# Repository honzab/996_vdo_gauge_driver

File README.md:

# Building an oil temperature gauge for Porsche 996

## Introduction

This project is about building an oil temperature gauge for a Porsche 911/996.

The car does not have a temperature gauge from the factory and neither does it expose the information on 
the CAN bus so that it can be read by an OBD-II reader.

People have developed different kind of solutions for this problem, but there was one that especially
caught my eye, both because of the design but also reversibility and accuracy of the solution.

## tl;dr
There's been some hiccups on the way, but I have succeeded in building a prototype that can display temperature 
values of my choosing. I have a code snippet that runs from 50ºC to 150ºC with a couple of seconds delay 
between each value. The gauge shows the values.

**I have NOT connected anything to the car yet!**

* [Schematics](vdo_gauge_driver_schematics/vdo_gauge_driver_rev0.2.pdf)
* [Code for ATTiny85](vdo_gauge_driver_software/vdo_gauge_driver_software.ino)

## Ahsai's design from 2014

Back in 2014, [Ahsai](https://rennlist.com/forums/members/32590-ahsai.html)
[published a design for a temperature gauge that uses the factory oil level/temperature sensor](https://rennlist.com/forums/996-forum/827720-oil-temp-gauge-using-the-built-in-oil-temp-sensor.html) by
tapping the sensor wire directy on its way to the ECU. This way, the factory ECU is still able to read the oil pressure,
but we can through the tap see it as well.

When you have access to the voltage from the sensor, you can choose to display it in any way you'd like. Back then
Ahsai chose to use the VDO gauge, which fits the design of the interior pretty well.

## Trying to build it in 2025

In April 2025 I decided to try to build it as well.

### Introduction

I looked at the original schematics, but some of the components have already been replaced by newer ones. This meant 
that I would need to redo the schematics, look at all the datasheets and find replacement components.

[Ahsai's Original Schematics](images/ExpressSCH-page-0.jpg)

The circuit itself is fairly simple and smart. It uses an ATTiny85 to convert the voltage from the sensor to a voltage
that drives the VDO gauge.

What we can use from the original design is the values for the sensor signal, or at least the polynomial that 
was used to approximate the conversion values.

### Problem #1, obsolete components

The components in the original design are not available anymore, so we need to find replacements.

For the voltage regulators, that's kind of easy. We can use

* [L7805](datasheets/L78.pdf) for 5V
* ~~[L7812](datasheets/L78.pdf) for 12V (turns out I don't need this one in the end)~~

For the op-amp, the L727M is not available anymore. Moreover it is not rail-to-rail, which means that if the
input drops all the way to 0V, the output will not be able to reach 0V. This is a problem since we need it to
be quite exact.

I set off to find a replacement and found a rail-to-rail op-amp which is easily available.

* [MCP6002](datasheets/mcp6002.pdf)

The microprocessor is still available without problems.

* [ATTiny85](datasheets/attiny85-20pu.pdf)

### Problem #2, the gauge is resistive-type

The original design suggests that you can drive the gauge with voltage. This does not work in reality. The sensor
paired with the gauge seems to be a [NTC thermistor](https://en.wikipedia.org/wiki/Thermistor#NTC_(negative_temperature_coefficient)).

This means that we cannot feed the gauge with the (amplified and converted) voltage from the Porsche sensor.

I am hoping that I can use an N-channel MOSFET to simulate the resistance. This should be drivable by 0-2.5V from the ATTiny85.
Calibration will be needed to get the right display readings.

Right now, I am not really sure how it could ever have worked for Ahsai.

**Solution**: Use a MOSFET to simulate the resistance. I've picked the [2N7000](datasheets/2N7000.pdf) for this.

### Problem 3, the MOSFET is not linear and precise enough

With only the transistor simulating the resistance, I am getting fairly unprecise readings. This is not very good, because
in the beginning of the temperature scale is where I need the most precision, since the oil temperature will likely be
between 50-100°C most of the time.

By making the ATTiny85 output a consistent voltage changes, I could observe the gauge displaying different values depending
on where the needle was moving from.

**Solution**: After a bit of research, it turns out that I could use a current sink with the one op-amp that I have left from the MCP6002.
It was a bit tricky to figure out what the resistor value should be between the source and ground.

#### Problem 3.1, the gauge's internal resistance

Most likely the gauge has some internal resistance and is applying certain voltage on the sensor wire, measuring the voltage drop.

The voltage between the signal pin and ground seems to be 7.5V.

Measuring current using some different resistor values, I got to the following

| R (Ω) | I (mA) | R_int (Ω) |
|-------|--------|-----------|
| 47    | 50     | 103,00    |
| 0     | 59     | 127,12    |

This means, I think, that the internal resistance is likely 100Ω. My cheap multimeter is not very precise, so I am not exactly
sure, but it's at least some ballpark number.

#### Problem 3.2, the current sink values

If we take the above, then we can calculate the currents we want to have through the sensor wire.

* Maximum resistance: 130Ω
* Minimum resistance: 20Ω

Then the currents are:

* Maximum resistance current then: R = 7.5V / 130Ω = 57.69mA
* Minimum resistance current then: R = 7.5V / 20Ω = 375mA

Knowing that we will be driving the MOSFET with a voltage between 0-5V from the ATTiny85, we can calculate
the resistance needed to achieve the above currents, again at least ballpark values.

With R of 22Ω we get these with the different voltages:

| V   | mA          |
|-----|-------------|
| 0,1 | 4,545454545 |
| 1   | 45,45454545 |
| 2   | 90,90909091 |
| 3   | 136,3636364 |
| 4   | 181,8181818 |
| 5   | 227,2727273 |

This is not really exactly what we need, but it is good enough for now. The 5V input would be anyways going over what
the MOSFET can do.

#### Problem 3.3, the op-amp used cannot drive so much current

The MCP6002 op-amp cannot drive as much current as we need. Luckily though, it seems to be able to run the gauge's
pointer all the way to 140ºC, which is good enough for me (for now at least).

### Getting to what value is what

In the original design, Ahsai used Durametric software to get the temperature values (in F) and mapped them to the
voltage observed on the sensor wire.

> [!NOTE]
> I would like to maybe borrow someone's Durametric and check myself. But as of now (May 2025), I trust this data.

[Ahsai's original values](images/Drawing1.jpg), with the polynomial approximated (in F):

```
y = 8.5645 * x^4 - 59.284 * x^3 + 160.76 * x^2 - 245.49x + 299.24
R^2 = 0.9997
```

We can then use this information to build the table of values in Celsius, using a simple [python script](engine_sensor_voltage_temperature.py).
(run `brew install gnuplot` (MacOS) if you don't have it already).

| voltage   | °C       | F       |
|-----------|----------|---------|
| 2.90V     | 37.32°C  | 99.18F  |
| 2.80V     | 36.25°C  | 97.25F  |
| 2.70V     | 35.90°C  | 96.62F  |
| 2.60V     | 36.17°C  | 97.11F  |
| 2.50V     | 36.95°C  | 98.50F  |
| ...        | ...      | ...     |
| 0.40V     | 106.22°C | 223.19F |
| 0.30V     | 114.74°C | 238.53F |
| 0.20V     | 124.51°C | 256.11F |
| 0.10V     | 135.69°C | 276.24F |
| 0.00V     | 148.47°C | 299.24F |

_(I've shortened the table, all the values can be obtained by running the script.)_

### What's needed

TODO: add list of components

#### Mounting

TODO: Could [this be something](https://www.amazon.com/dp/B0018ALWOE/ref=sspa_dk_detail_1?psc=1&pd_rd_i=B0018ALWOE&pd_rd_w=7b38W&content-id=amzn1.sym.7446a9d1-25fe-4460-b135-a60336bad2c9&pf_rd_p=7446a9d1-25fe-4460-b135-a60336bad2c9&pf_rd_r=N8RSV7SSJCJFGKZRW0Q5&pd_rd_wg=nYLRA&pd_rd_r=9f5e788e-8383-43bf-b18c-378f6cef02c4&s=electronics&sp_csd=d2lkZ2V0TmFtZT1zcF9kZXRhaWw)?

#### The DME connectors research

The original Ahsai's links to the connectors point to Mouser, but they are not available anymore.

I think that these should do it, but the only way to know is to order some and try them out.

| type   | old part number | width           | style              | new part number | copied description                                        |
|--------|-----------------|-----------------|--------------------|-----------------|-----------------------------------------------------------|
| male   | 963730-1        | pin 0.63x0.63mm | Micro Quadlock MQS | 5-963716-1      | male; 0.63mm; tinned; 0.2÷0.35mm2; 24AWG÷22AWG; crimped   |
| female | 963729-1        | n/a             | Micro Quadlock MQS | 5-963715-1      | female; 0.63mm; tinned; 0.5÷0.75mm2; 20AWG÷18AWG; crimped |

* 5-963715-1 female [digikey.se](https://www.digikey.se/en/products/detail/te-connectivity-amp-connectors/5-963715-1/10478401)
* 5-963716-1 male [digikey.se](https://www.digikey.se/en/products/detail/te-connectivity-amp-connectors/5-963716-1/5437656)

Potentially [a crimping tool from Amazon](https://www.amazon.se/iCrimp-Crimping-AWG28-20-Terminals-Connectors/dp/B078WNZ9FW/ref=asc_df_B078WNZ9FW?mcid=1af05a2f26a63e6584890cf14fcee144&tag=shpngadsglede-21&linkCode=df0&hvadid=719622306849&hvpos=&hvnetw=g&hvrand=17724259167483025586&hvpone=&hvptwo=&hvqmt=&hvdev=c&hvdvcmdl=&hvlocint=&hvlocphy=9217559&hvtargid=pla-527283798174&language=sv_SE&gad_source=1&th=1).

### Prepping the Arduino IDE

Add this to Preferences / Additional Boards Manager URLs:

```
https://raw.githubusercontent.com/damellis/attiny/ide-1.6.x-boards-manager/package_damellis_attiny_index.json
```

Then go to Boards Manager, search for `attiny` and install it.

Then Choose:

* Tools > Board > attiny > `ATtiny25/45/85`
* Tools > Clock > `8 MHz (internal)`
* Tools > Processor > `ATtiny85`
* Tools > Programmer > `USBtinyISP`

Then do `Tools > Burn Bootloader`.

### Compiling and uploading your code

> [!NOTE]
> If you get error compiling on an Apple silicon Mac (like this `bad CPU type in executableCompilation`), run `softwareupdate --install-rosetta`

> [!NOTE]
> For any new chip that you are programming, you need to burn the bootloader first!

Write your code, compile with `Sketch > Verify/Compile` and upload with `Sketch > Upload`.

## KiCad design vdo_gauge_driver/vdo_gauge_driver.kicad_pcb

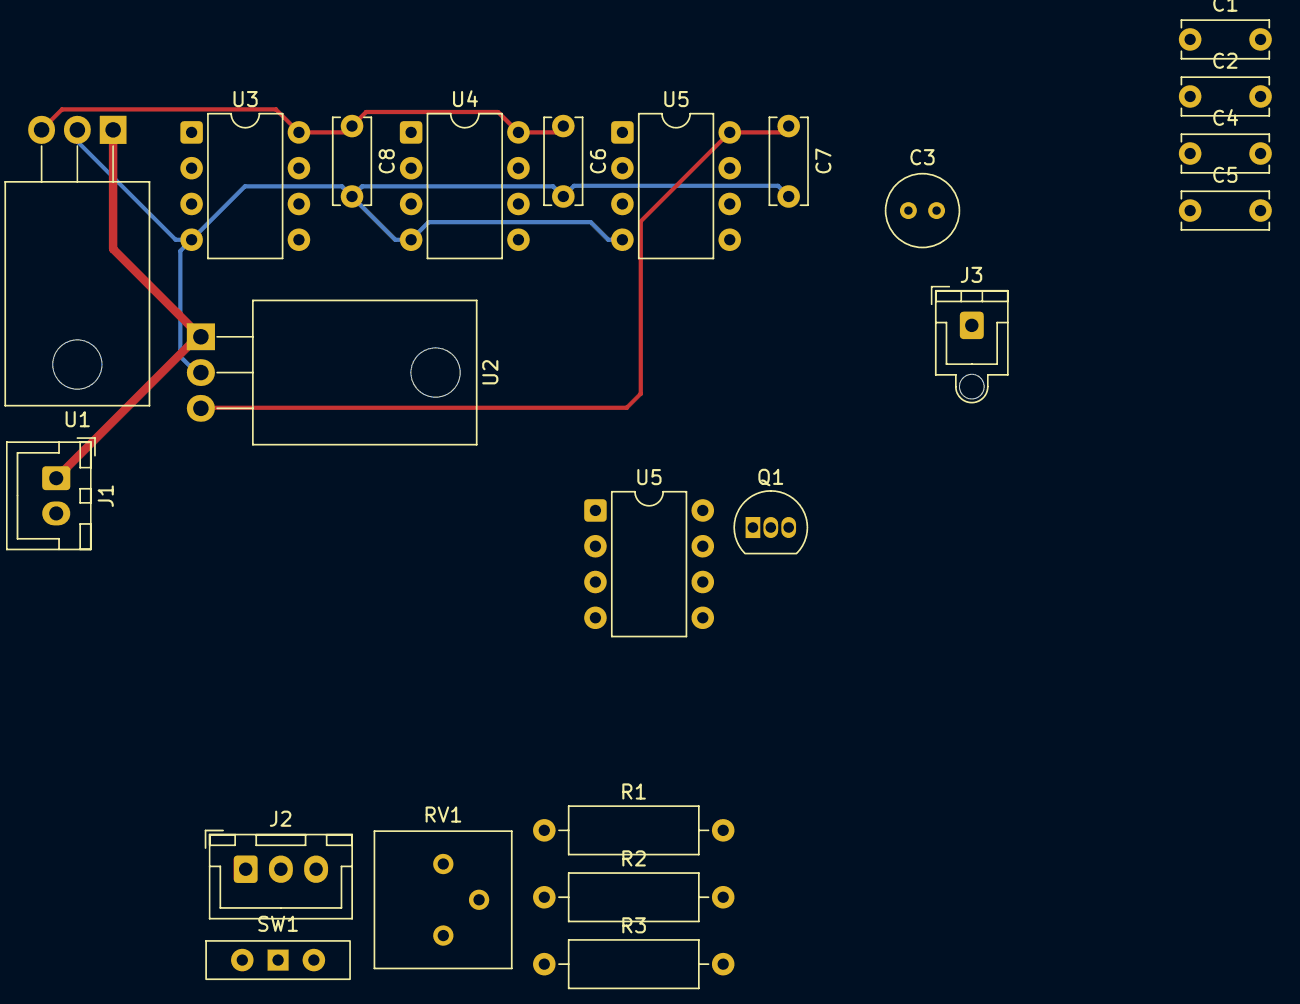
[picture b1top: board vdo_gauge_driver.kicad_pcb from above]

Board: 2 copper layers, 23 parts (0 on the bottom side), 13 nets.

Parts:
C1, C4: 0.33uF; C_Disc_D6.0mm_W2.5mm_P5.00mm
C2, C5, C6, C7, C8: 0.1uF; C_Disc_D6.0mm_W2.5mm_P5.00mm
C3: 10uF; C_Radial_D5.0mm_H7.0mm_P2.00mm
J1: 12V and GND; JST_XH_B2B-XH-A_1x02_P2.50mm_Vertical
J2: 12V / Signal / GND; JST_XH_B3B-XH-A_1x03_P2.50mm_Vertical
J3: ECU Input; JST_XH_B1B-XH-AM_1x01_P2.50mm_Vertical
Q1: 2N7000; TO-92_Inline
R1: 1k; R_Axial_DIN0309_L9.0mm_D3.2mm_P12.70mm_Horizontal
R2, R3: 10k; R_Axial_DIN0309_L9.0mm_D3.2mm_P12.70mm_Horizontal
RV1: R_Potentiometer; Potentiometer_Bourns_3386P_Vertical
SW1: SW_SPDT; SW_Slide-03_Wuerth-WS-SLTV_10x2.5x6.4_P2.54mm
U1: L7805; TO-220-3_Horizontal_TabDown
U2: L7812; TO-220-3_Horizontal_TabDown
U3: MCP6002-xP; DIP-8_W7.62mm
U4: ATtiny85-20P; DIP-8_W7.62mm
U5, U5#2: LM2904; DIP-8_W7.62mm

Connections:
12V: C1.1, C4.1, J1.1, U1.1 (IN), U2.1 (IN)
/0-10V: R3.1, U5.1
/5V: C2.1, C6.1, C8.1, RV1.1, U1.3 (OUT), U3.8 (V+), U4.8 (VCC)
/12V regulated: C5.1, C7.1, J2.1, U2.3 (OUT), U5.8 (V+), U5#2.8 (V+)
/Attiny85 out 0-5V: R1.1, U4.6 (PB1)
/Drain: J2.2, Q1.3 (D)
/ECU Input: J3.1, SW1.3 (C)
/Input: SW1.1 (A), U3.3 (+)
/Smoothed Signal Out / Gate: C3.1, Q1.2 (G), R1.2
/Testing 0-5V: RV1.2, SW1.2 (B)
/op-amped signal: U3.1, U3.2 (-), U4.2 (XTAL1/PB3)
GND: C1.2, C2.2, C3.2, C4.2, C5.2, C6.2, C7.2, C8.2, J1.2, J2.3, Q1.1 (S), R2.2, RV1.3, U1.2 (GND), U2.2 (GND), U3.4 (V-), U4.4 (GND), U5.4 (V-), U5#2.4 (V-)
unnamed: R2.1, R3.2, U5.2 (-)

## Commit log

2025-05-04 Updated schematics
2025-05-04 KiCad project cleanup
2025-05-09 Update the cad drawings
2025-05-09 Move name to Silklayer
2025-05-14 Adding datasheets, working on README, python generated graph and values
2025-05-19 Rename L78 datasheet
2025-05-19 Change to use the MOSFET
2025-05-21 Working, but unstable
2025-05-22 Readme WIP
2025-05-22 Fix link to the male MQS connector
2025-05-22 Add the sketch
2025-05-24 Major commit :)
2025-05-24 Cleanup root folder
2025-05-24 12V voltage regulator not needed
2025-05-24 Make the gif loop
2025-05-27 Rename the schematics folder
2025-05-27 Closer to final version of the c code
2025-05-27 Adding the ATTiny software
2025-05-27 Add makefile to test
2025-05-27 Move mqs description
2025-06-05 Update arduino instructions
2025-06-14 Update the PCB image
2025-07-05 Add DME7.8 pins description
